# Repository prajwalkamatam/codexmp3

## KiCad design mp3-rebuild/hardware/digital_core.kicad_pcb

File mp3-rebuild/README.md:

# MP3 hardware rebuild — checkpoint, not a production release

This archive is NOT the completed MP3 player and is NOT a fabrication package.
It replaces the previous ad-hoc symbol recovery with a separately scoped digital
core schematic and a routed digital-core PCB prototype. The original complete-board
PCB is still invalid and must not be manufactured. No production-ready PCB,
Gerbers, or assembly files are supplied.

## Completed and checked

- Built a 52-symbol digital-core schematic (50 physical components plus two
  external-supply flags) with explicit pin assignments.
- Used Espressif's official ESP32-WROVER-E symbol and footprint, release 2.0.6,
  commit 3343256bd40fa1d049b444767d4b935ad93ba91f.
- Added EN reset RC, boot/reset switches, boot strapping, bias resistors,
  decoupling, battery ADC divider/filter, TCA9534 expander and seven buttons.
- Provided explicit interfaces for the intended GC9A01 display, SPI SD socket,
  regulated power, UART, I2S audio, and status signals. These interfaces are
  engineering boundaries, not substitutes for the missing product circuits.
- Bundled the symbol and footprint definitions required to open the schematic.
- KiCad 9.0.2 ERC: zero errors, zero warnings, exit status 0.
- KiCad XML export: completed with no annotation warning after reference cleanup.
- Exported connectivity: all 160 physical component-pin assignments match the
  digital-core connection model; specific ESP32 GPIO/reserved-pad assertions pass.
- Exported PDF and visually inspected the sheet. Zoom in for pin labels.
- Routed hardware/digital_core.kicad_pcb with 50 footprints and 36 named nets.
  KiCad 9.0.2 DRC with all severities and schematic parity reports zero
  violations, zero unconnected items and zero schematic parity issues.
  The underlying DRC command completed with exit status 0.
- Independently checked all 160 component-pin net assignments after importing
  copper. Reserved pads remain unassigned. See reports/routed-pad-check.txt.
- Routing was restored on 2026-11-14 using Freerouting 2.0.1. Both routing inputs
  and sessions are retained in engineering/. The ESP32 antenna keep-out is
  retained on both actual copper layers (F.Cu and B.Cu); the local library rule
  area was made specific to those two layers to match the board layer stack.
- The board remains a prototype with roomy 160 x 100 mm placement and 0.2 mm
  routing rules. Power-current capability, return paths, decoupling placement,
  and signal integrity require engineering review and physical validation.

Open hardware/digital_core.kicad_pro in KiCad 9 or newer. The project includes
hardware/digital_core.kicad_sch and hardware/digital_core.kicad_pcb.
See reports/digital-erc.txt, reports/digital-pcb-drc.txt, and
reports/netlist-check.txt for scoped evidence.
Open the extracted project with its matching .kicad_pcb, .kicad_sch and libraries
together. A .kicad_pro file contains project settings, not the routed copper.
Use the latest routed ZIP; the older GitHub commit 77369ca contains an unrouted PCB.
A clean ERC checks schematic rules; it does not prove analog performance,
component ratings, routing, power integrity, or physical operation.

## Historical datasheet-access blocker (not retested during routing)

During the earlier circuit-rebuild session, an HTTPS request to
https://www.ti.com/lit/ds/symlink/tpa6132a2.pdf returned
403 Forbidden at the proxy CONNECT stage. TLS checking was not disabled and the
network restriction was not bypassed.

Required manufacturer-domain additions were saved to the environment draft,
preserving the existing dl.espressif.com entry:
- www.ti.com
- ww1.microchip.com
- www.silabs.com
- www.waveshare.com
- files.waveshare.com
- www.espressif.com
- docs.espressif.com

Review/save the network changes in environment settings and publish the updated
environment configuration. A saved draft alone does not change running access.
After application, retest the affected request before resuming circuit selection.

## Remaining product work

1. Verify the exact Waveshare 1.28-inch GC9A01 module revision, supply, BL input,
   connector order, and mechanical drawing. J2 is the proposed carrier interface;
   do not connect an old ST7789 cable by position.
2. Select and verify the protected 1S 2000 mAh cell. Confirm 4.2 V termination,
   500 mA charging compatibility, temperature sensing, polarity and protection.
3. Rebuild the charger and load-sharing supply from manufacturer references.
   Evaluate MCP73871 power-path charging and a buck-boost regulator capable of
   the complete 3.3 V load at minimum battery voltage. The original AP2112 LDO
   does not maintain 3.3 V over the full single-cell discharge range. Do not
   finalize component values from symbol names or an ERC result.
4. Complete PCM5102A analog supplies, charge pump, output filtering and mode pins.
   Evaluate TPA6132A2 as a concrete headphone-amplifier replacement for the
   original invalid MAX97220A MPN/footprint combination, using its datasheet.
5. Complete the USB-C CC termination, ESD, CP2102N supplies and programming
   circuit, and the actual microSD and headphone socket circuits.
6. Merge sheets into the full product schematic, resolve the complete BOM,
   verify every symbol-to-pad mapping and run full-design ERC.
7. Place and route a new PCB from that verified netlist. Preserve RF antenna
   exclusion, switching-current loops, continuous return paths, analog layout,
   connector mechanics and required thermal copper. Run full DRC and parity.
8. Generate fabrication/assembly outputs only from the final checked board.
9. Implement missing firmware functionality: audio_player_play_file currently
   only updates metadata/state and uses a hardcoded duration. There is no MP3
   decoder producer feeding the PCM ring buffer. The Bluetooth path only delays.
   The display driver remains ST7789-specific. These are confirmed source-code
   gaps, not environment failures.
10. Build and test a prototype: current-limited rail bring-up, charger termination
    and temperature behavior, boot/flash, GC9A01 display, SD access, decoded wired
    and Bluetooth audio, RF operation, noise, battery life and thermal margins.

## Reproduction

With Python 3 and KiCad 9.0.2 standard libraries installed:
  python3 build_digital.py
  kicad-cli sch erc --exit-code-violations -o reports/digital-erc.txt hardware/digital_core.kicad_sch
  kicad-cli sch export netlist --format kicadxml -o engineering/digital_core.xml hardware/digital_core.kicad_sch
  python3 check_netlist.py
  /usr/bin/python3 build_pcb.py
  /usr/bin/python3 apply_routing.py engineering/digital_core.ses
  /usr/bin/python3 apply_routing.py engineering/finish.ses
  kicad-cli pcb drc --schematic-parity --severity-all --exit-code-violations -o reports/digital-pcb-drc.txt hardware/digital_core.kicad_pcb
  kicad-cli sch export pdf -o engineering/digital_core.pdf hardware/digital_core.kicad_sch

Run KiCad commands sequentially because they can update project settings.
The routing sessions apply only to the current component positions and netlist.
If you change either, generate new routing rather than replaying the sessions.
Preserve the bundled official footprint under hardware/libraries/Local.pretty.
3D model paths in standard footprints may refer to an installed KiCad model pack;
3D model availability was not validated and is not included in the ERC claim.

Source licenses and Espressif release source are in sources/. The original
repository's tracked mp3.zip was preserved. This checkpoint makes no certification,
production-release, or end-to-end functionality claim.

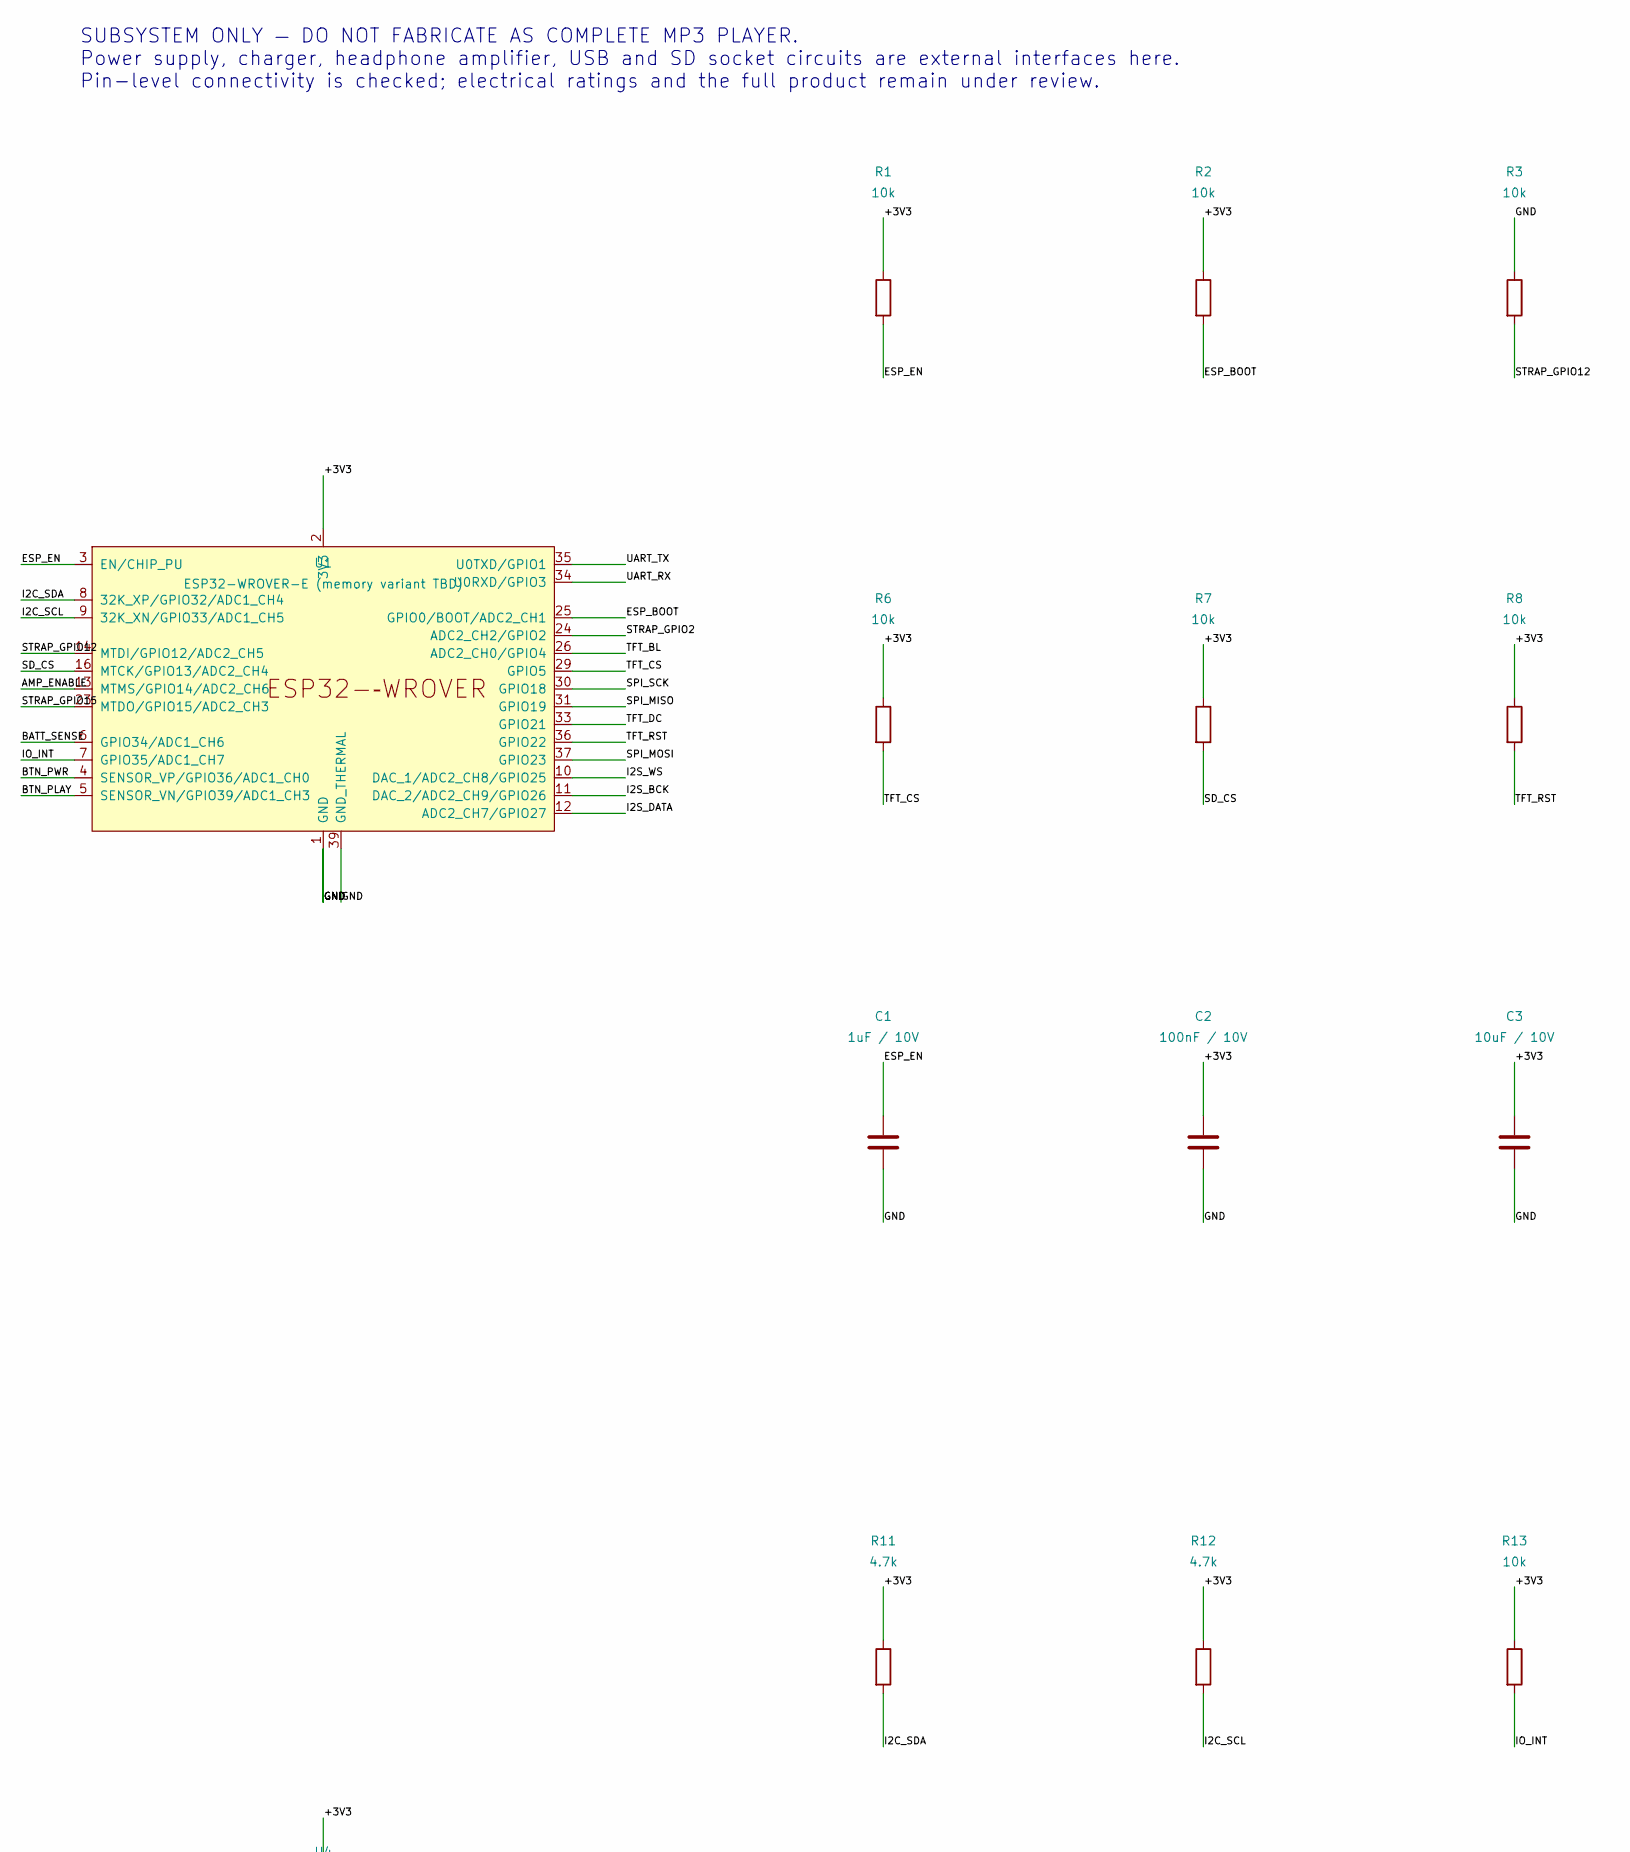
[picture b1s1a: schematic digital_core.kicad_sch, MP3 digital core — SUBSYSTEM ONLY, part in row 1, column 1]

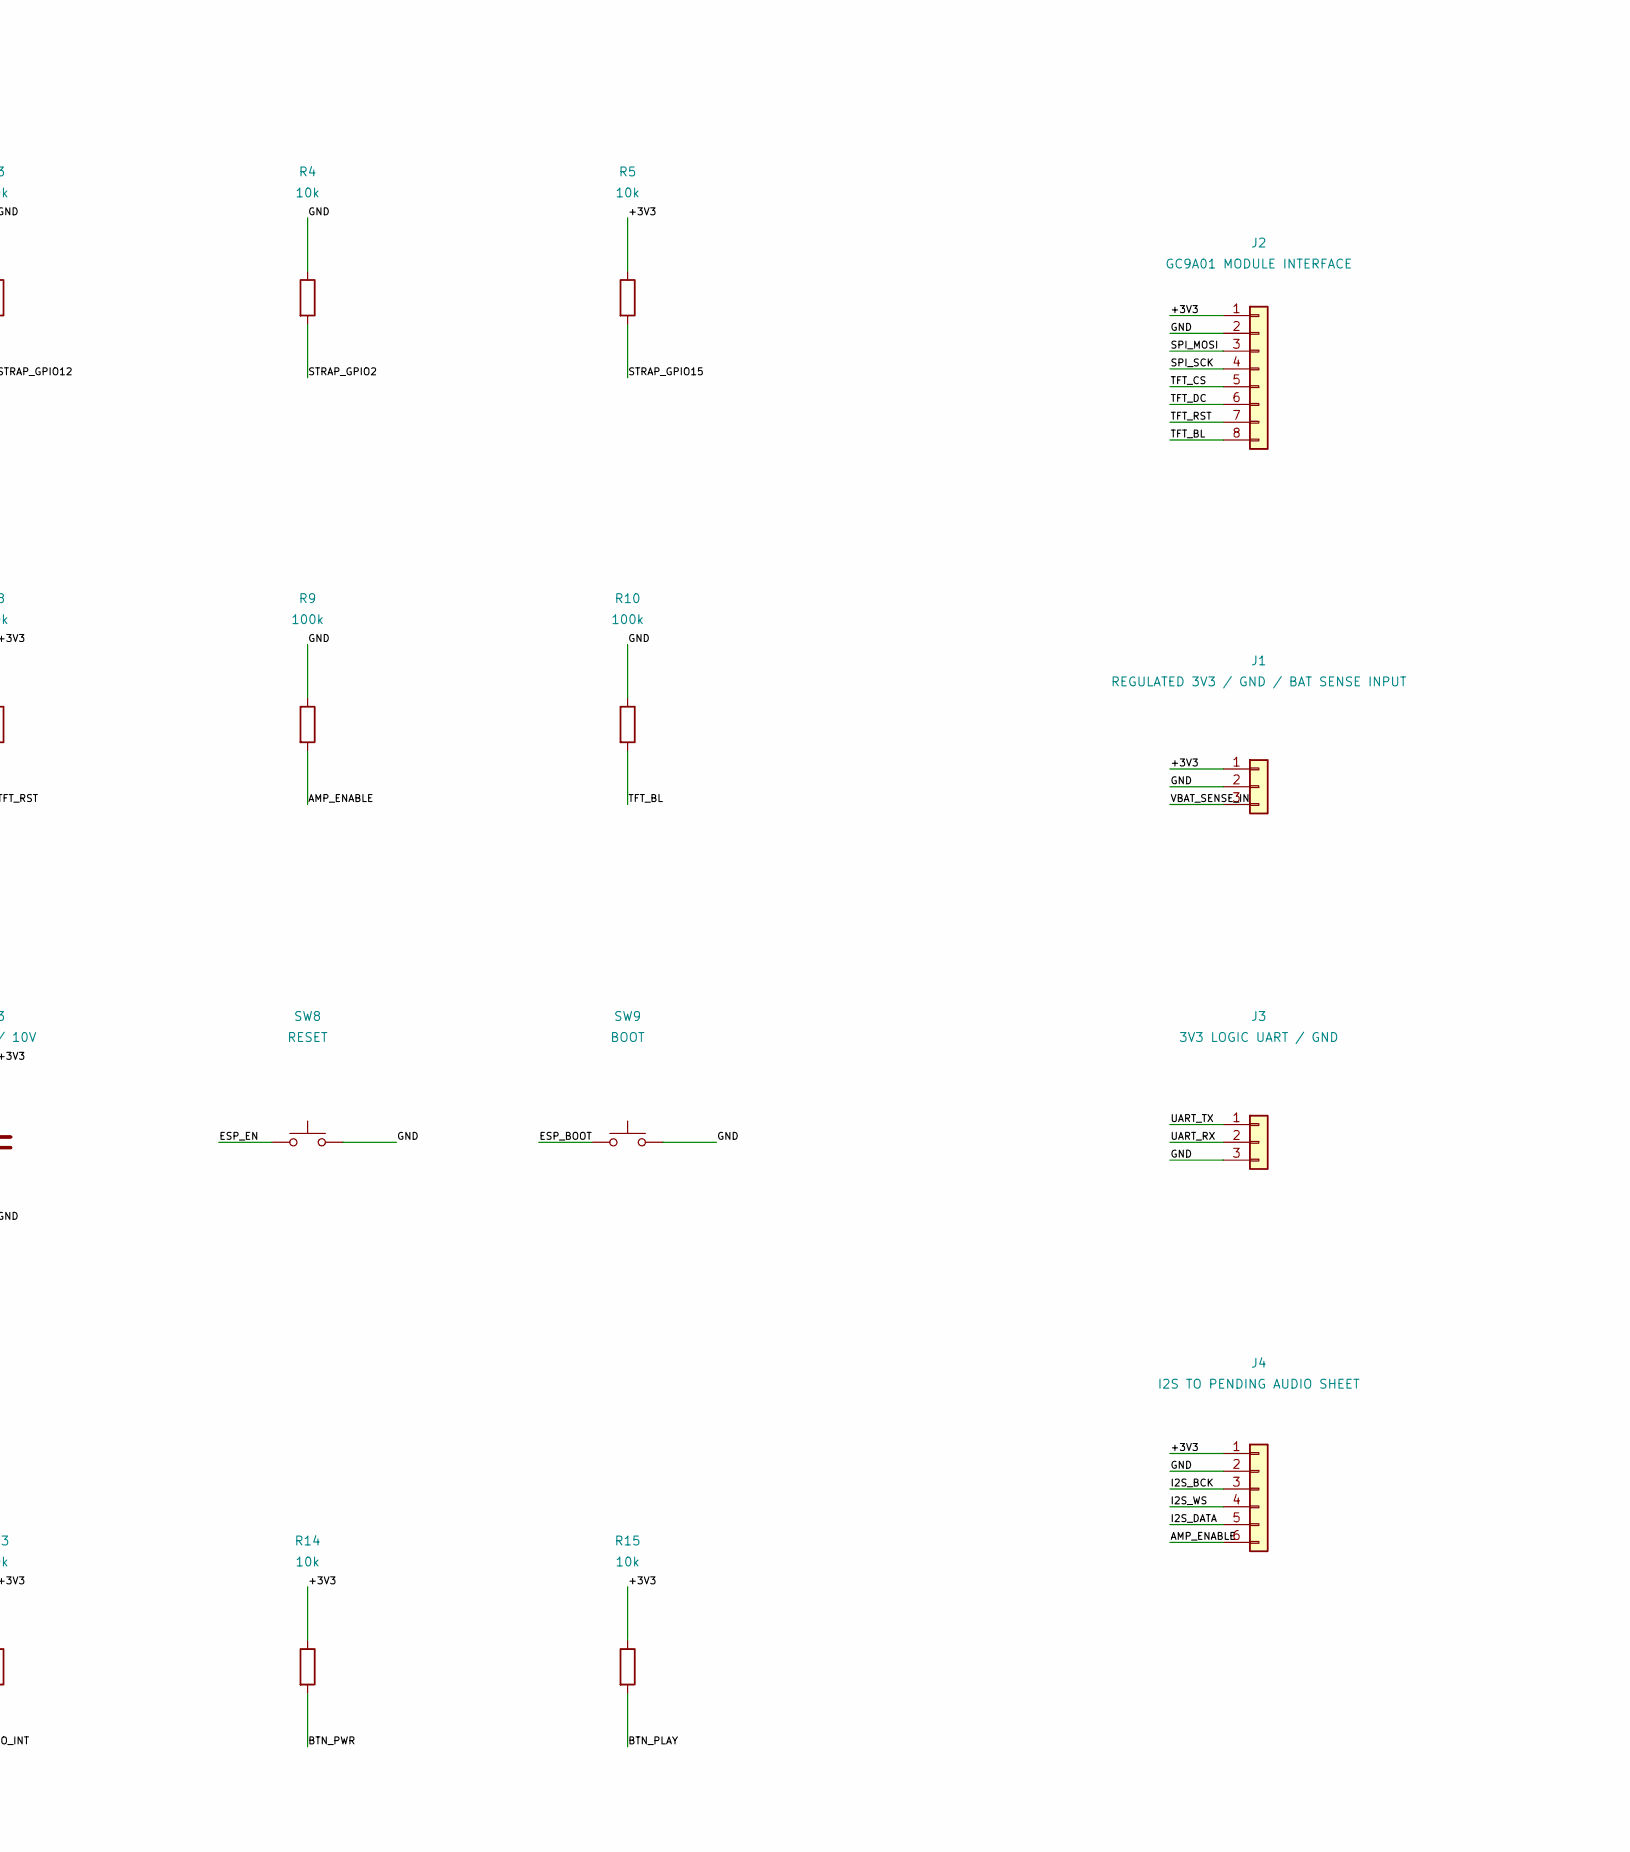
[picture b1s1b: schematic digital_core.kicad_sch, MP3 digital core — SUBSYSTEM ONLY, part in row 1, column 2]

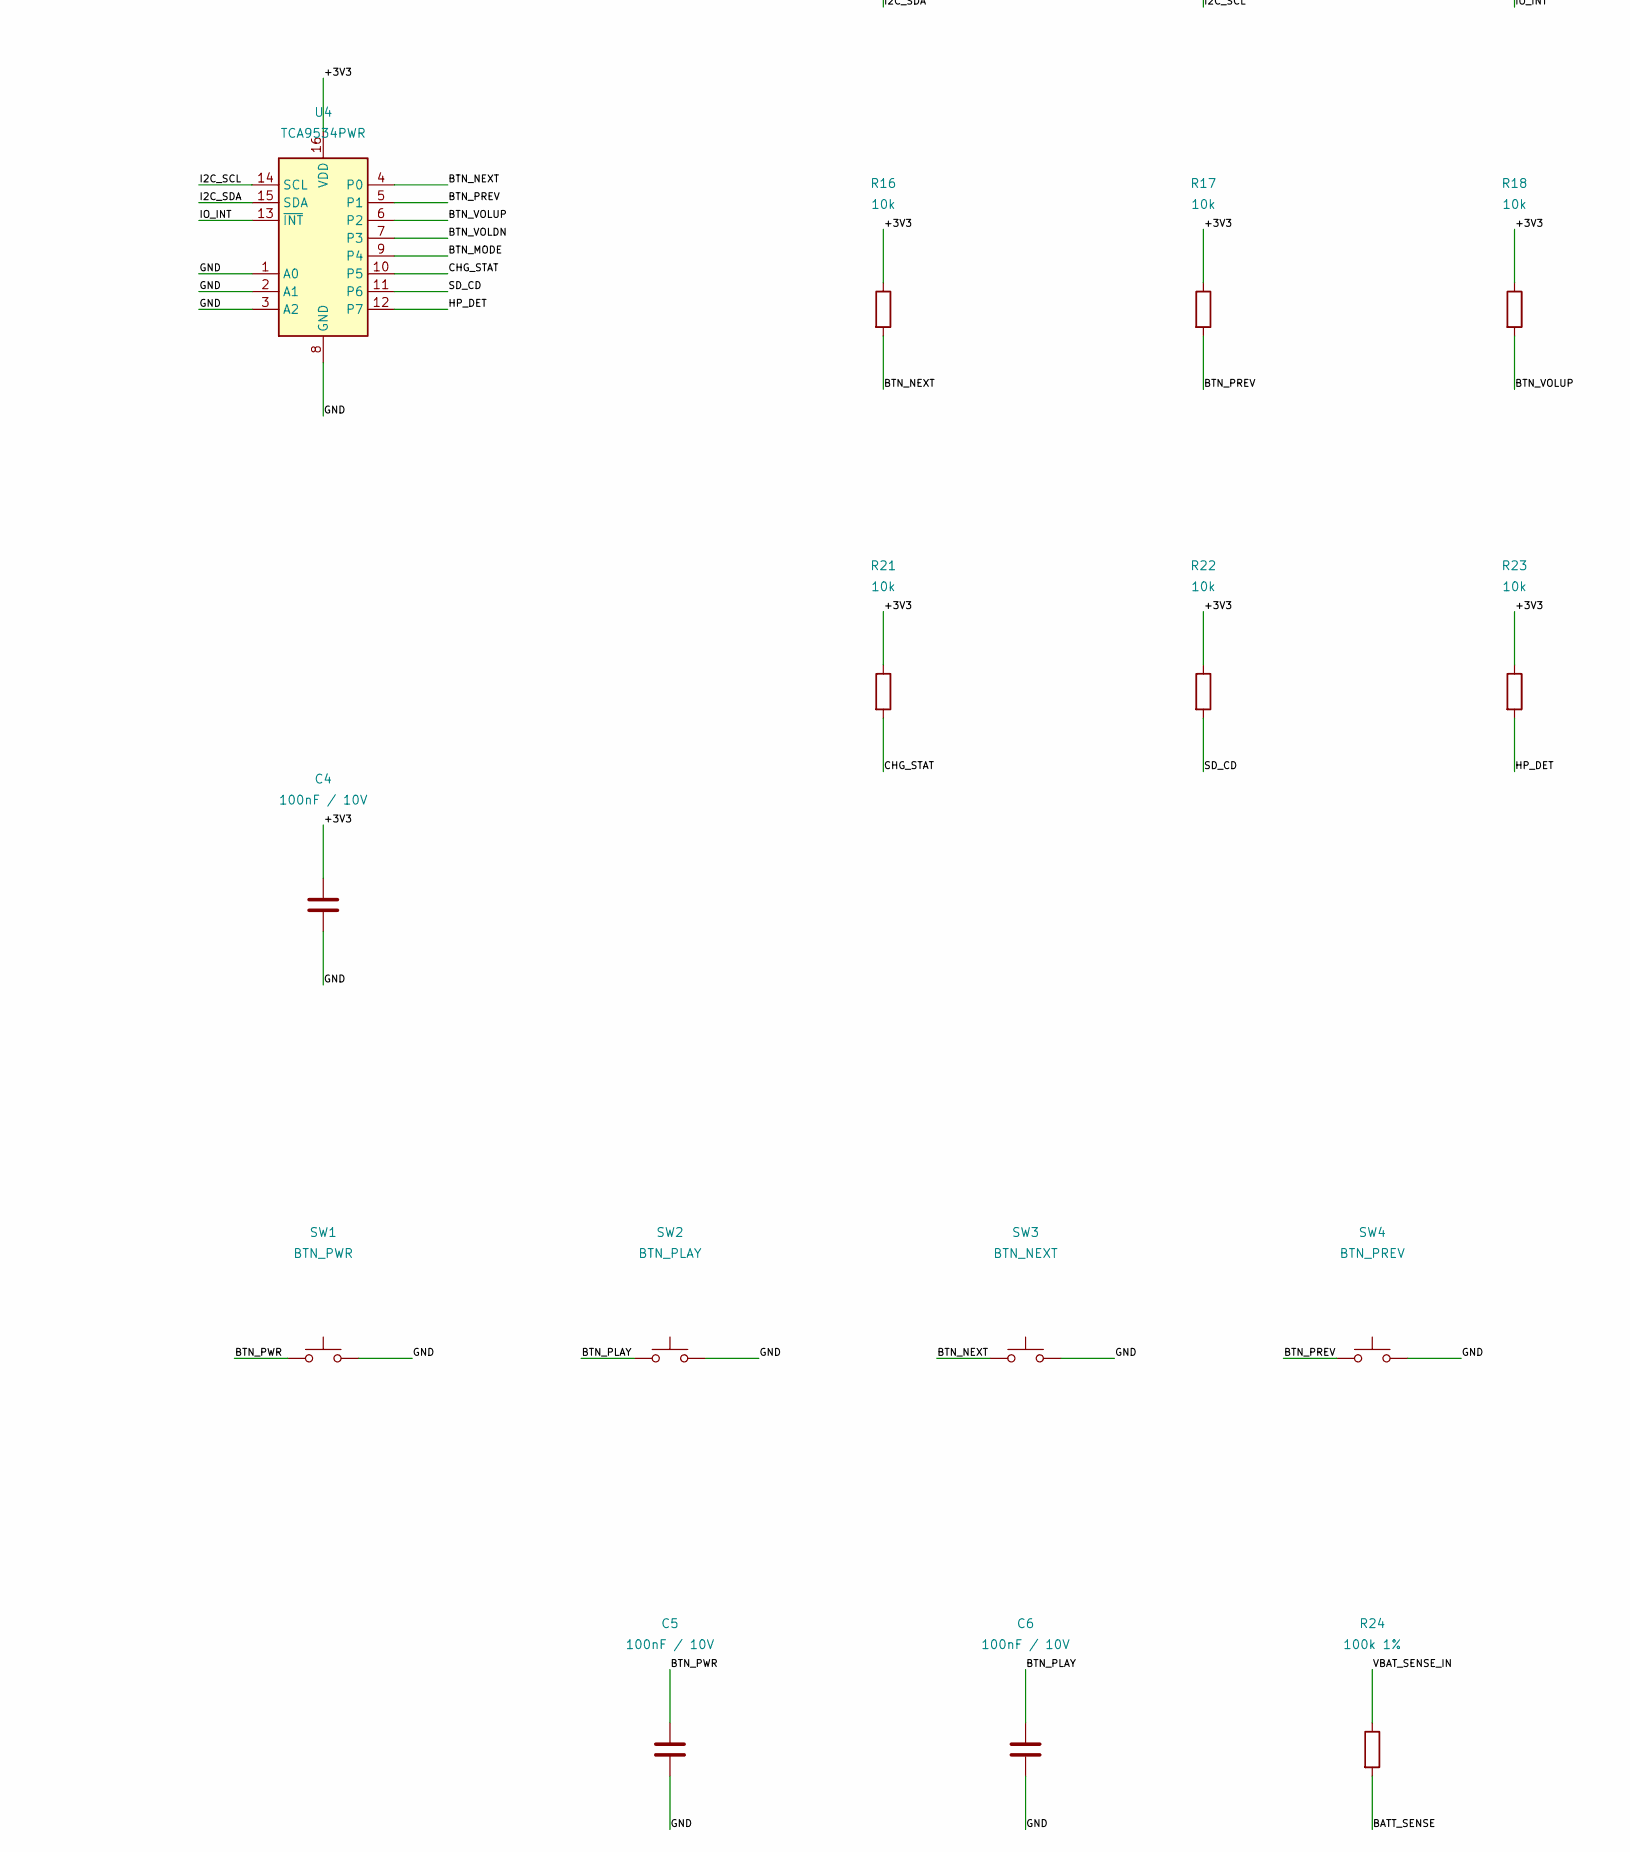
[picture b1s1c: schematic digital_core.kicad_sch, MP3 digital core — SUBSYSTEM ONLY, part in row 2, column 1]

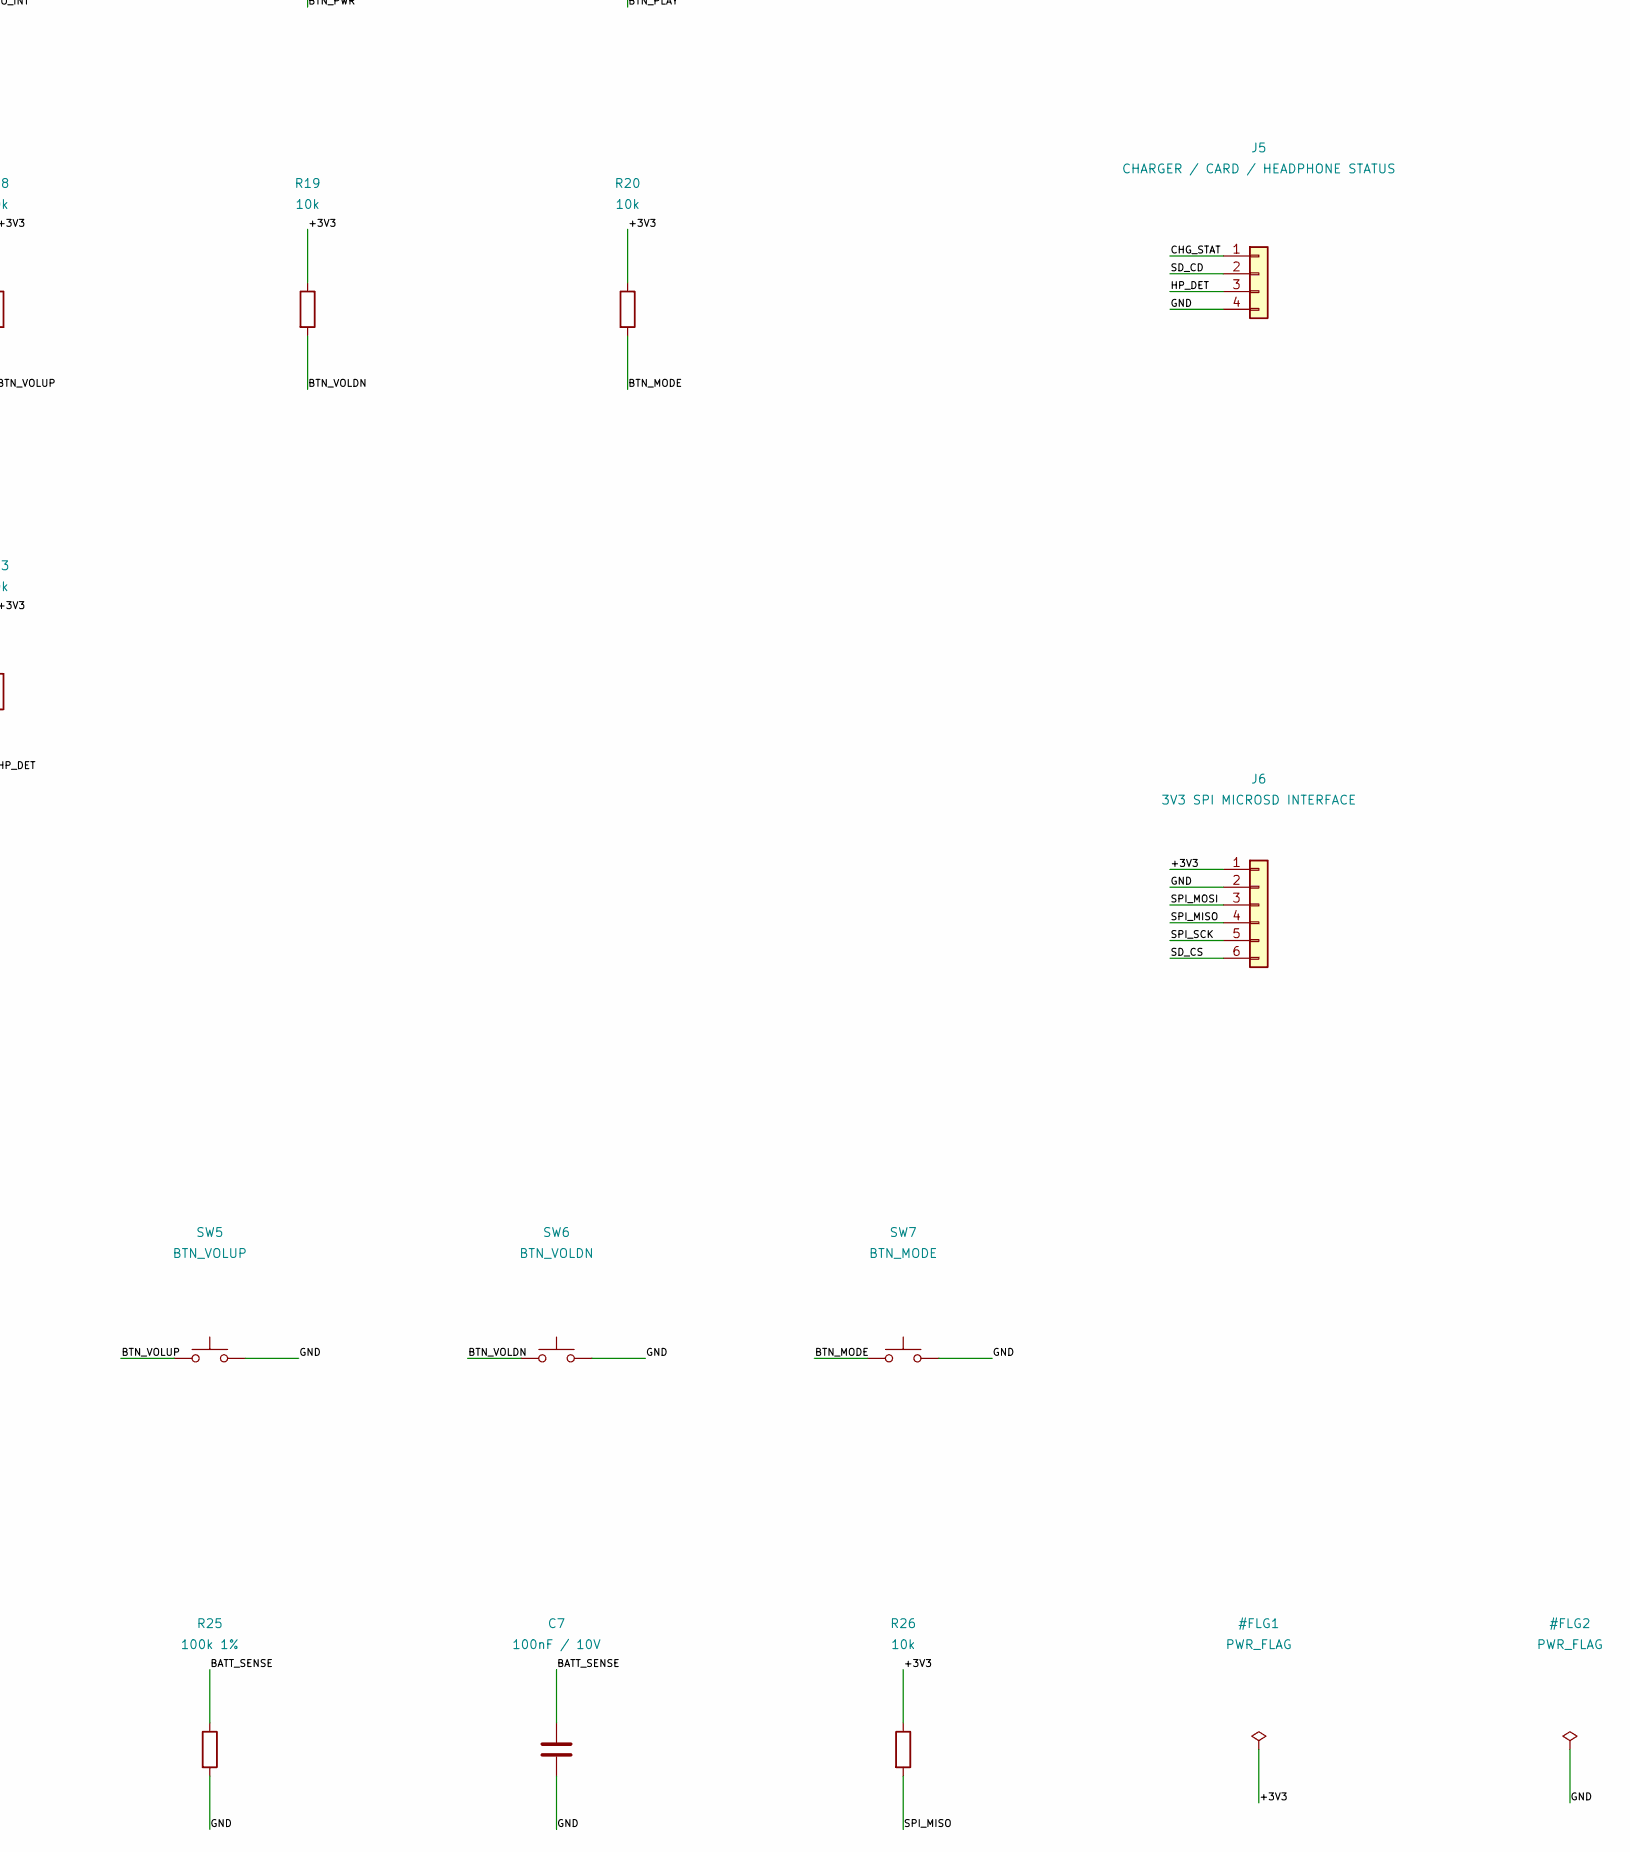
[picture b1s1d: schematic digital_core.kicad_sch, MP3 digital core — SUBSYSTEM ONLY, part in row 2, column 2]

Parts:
C1: 1uF / 10V; C_0603_1608Metric
C2, C4, C5, C6, C7: 100nF / 10V; C_0603_1608Metric
C3: 10uF / 10V; C_0805_2012Metric
J1: REGULATED 3V3 / GND / BAT SENSE INPUT; PinHeader_1x03_P2.54mm_Vertical
J2: GC9A01 MODULE INTERFACE; PinHeader_1x08_P2.54mm_Vertical
J3: 3V3 LOGIC UART / GND; PinHeader_1x03_P2.54mm_Vertical
J4: I2S TO PENDING AUDIO SHEET; PinHeader_1x06_P2.54mm_Vertical
J5: CHARGER / CARD / HEADPHONE STATUS; PinHeader_1x04_P2.54mm_Vertical
J6: 3V3 SPI MICROSD INTERFACE; PinHeader_1x06_P2.54mm_Vertical
R1, R2, R3, R4, R5, R6, R7, R8, R13, R14, R15, R16, R17, R18, R19, R20, R21, R22, R23, R26: 10k; R_0603_1608Metric
R9, R10: 100k; R_0603_1608Metric
R11, R12: 4.7k; R_0603_1608Metric
R24, R25: 100k 1%; R_0603_1608Metric
SW1: BTN_PWR; SW_SPST_TL3342
SW2: BTN_PLAY; SW_SPST_TL3342
SW3: BTN_NEXT; SW_SPST_TL3342
SW4: BTN_PREV; SW_SPST_TL3342
SW5: BTN_VOLUP; SW_SPST_TL3342
SW6: BTN_VOLDN; SW_SPST_TL3342
SW7: BTN_MODE; SW_SPST_TL3342
SW8: RESET; SW_SPST_TL3342
SW9: BOOT; SW_SPST_TL3342
U1: ESP32-WROVER-E (memory variant TBD); ESP32-WROVER-E
U4: TCA9534PWR; TSSOP-16_4.4x5mm_P0.65mm

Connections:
/+3V3: C2.1, C3.1, C4.1, J1.1, J2.1, J4.1, J6.1, R1.1, R2.1, R5.1, R6.1, R7.1, R8.1, R11.1, R12.1, R13.1, R14.1, R15.1, R16.1, R17.1, R18.1, R19.1, R20.1, R21.1, R22.1, R23.1, R26.1, U1.2 (3V3), U4.16 (VDD)
/AMP_ENABLE: J4.6, R9.2, U1.13 (MTMS/GPIO14/ADC2_CH6)
/BATT_SENSE: C7.1, R24.2, R25.1, U1.6 (GPIO34/ADC1_CH6)
/BTN_MODE: R20.2, SW7.1, U4.9 (P4)
/BTN_NEXT: R16.2, SW3.1, U4.4 (P0)
/BTN_PLAY: C6.1, R15.2, SW2.1, U1.5 (SENSOR_VN/GPIO39/ADC1_CH3)
/BTN_PREV: R17.2, SW4.1, U4.5 (P1)
/BTN_PWR: C5.1, R14.2, SW1.1, U1.4 (SENSOR_VP/GPIO36/ADC1_CH0)
/BTN_VOLDN: R19.2, SW6.1, U4.7 (P3)
/BTN_VOLUP: R18.2, SW5.1, U4.6 (P2)
/CHG_STAT: J5.1, R21.2, U4.10 (P5)
/ESP_BOOT: R2.2, SW9.1, U1.25 (GPIO0/BOOT/ADC2_CH1)
/ESP_EN: C1.1, R1.2, SW8.1, U1.3 (EN/CHIP_PU)
/GND: C1.2, C2.2, C3.2, C4.2, C5.2, C6.2, C7.2, J1.2, J2.2, J3.3, J4.2, J5.4, J6.2, R3.1, R4.1, R9.1, R10.1, R25.2, SW1.2, SW2.2, SW3.2, SW4.2, SW5.2, SW6.2, SW7.2, SW8.2, SW9.2, U1.1 (GND), U1.15 (GND), U1.38 (GND), U1.39 (GND_THERMAL), U4.1 (A0), U4.2 (A1), U4.3 (A2), U4.8 (GND)
/HP_DET: J5.3, R23.2, U4.12 (P7)
/I2C_SCL: R12.2, U1.9 (32K_XN/GPIO33/ADC1_CH5), U4.14 (SCL)
/I2C_SDA: R11.2, U1.8 (32K_XP/GPIO32/ADC1_CH4), U4.15 (SDA)
/I2S_BCK: J4.3, U1.11 (DAC_2/ADC2_CH9/GPIO26)
/I2S_DATA: J4.5, U1.12 (ADC2_CH7/GPIO27)
/I2S_WS: J4.4, U1.10 (DAC_1/ADC2_CH8/GPIO25)
/IO_INT: R13.2, U1.7 (GPIO35/ADC1_CH7), U4.13 (~INT)
/SD_CD: J5.2, R22.2, U4.11 (P6)
/SD_CS: J6.6, R7.2, U1.16 (MTCK/GPIO13/ADC2_CH4)
/SPI_MISO: J6.4, R26.2, U1.31 (GPIO19)
/SPI_MOSI: J2.3, J6.3, U1.37 (GPIO23)
/SPI_SCK: J2.4, J6.5, U1.30 (GPIO18)
/STRAP_GPIO2: R4.2, U1.24 (ADC2_CH2/GPIO2)
/STRAP_GPIO12: R3.2, U1.14 (MTDI/GPIO12/ADC2_CH5)
/STRAP_GPIO15: R5.2, U1.23 (MTDO/GPIO15/ADC2_CH3)
/TFT_BL: J2.8, R10.2, U1.26 (ADC2_CH0/GPIO4)
/TFT_CS: J2.5, R6.2, U1.29 (GPIO5)
/TFT_DC: J2.6, U1.33 (GPIO21)
/TFT_RST: J2.7, R8.2, U1.36 (GPIO22)
/UART_RX: J3.2, U1.34 (U0RXD/GPIO3)
/UART_TX: J3.1, U1.35 (U0TXD/GPIO1)
/VBAT_SENSE_IN: J1.3, R24.1

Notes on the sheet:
SUBSYSTEM ONLY — DO NOT FABRICATE AS COMPLETE MP3 PLAYER. Power supply, charger, headphone amplifier, USB and SD socket circuits are external interfaces here. Pin-level connectivity is checked; electrical ratings and the full product remain under review.

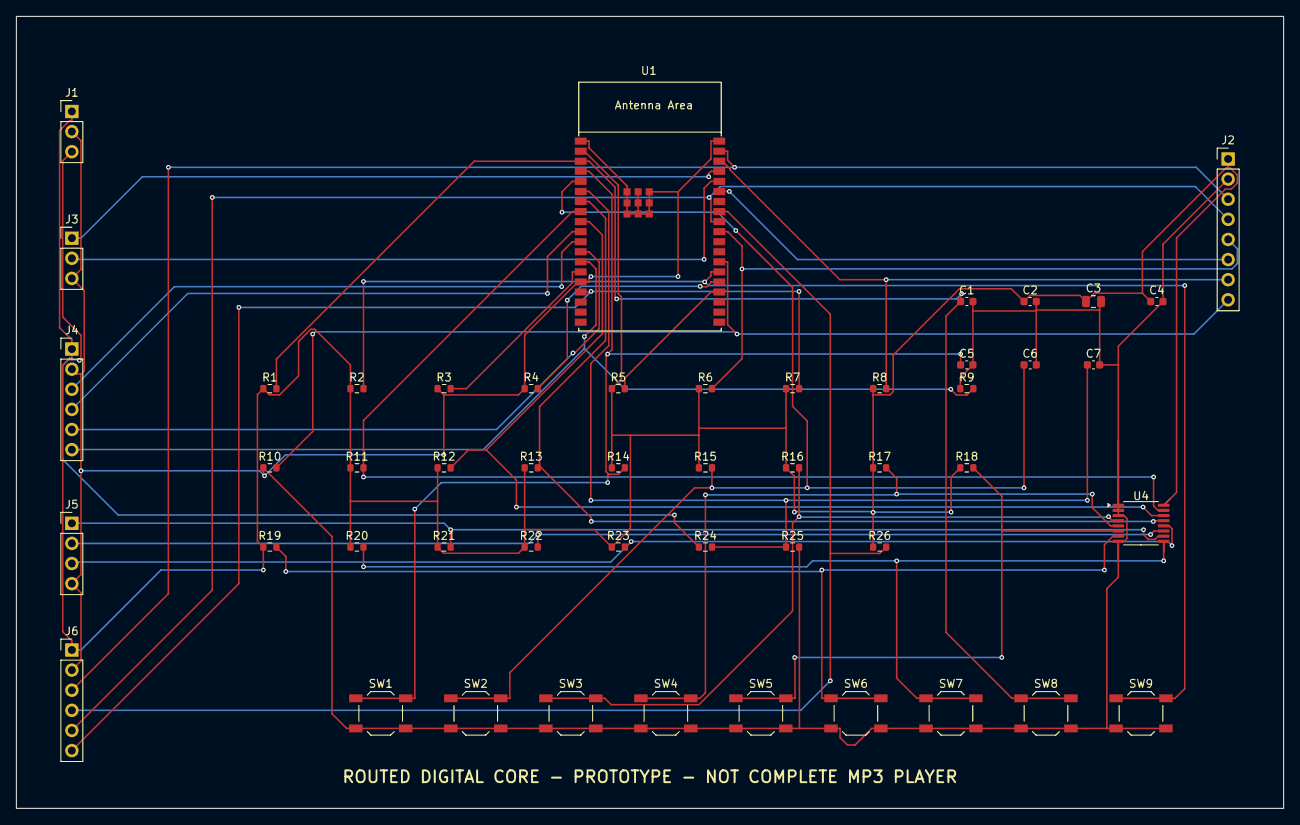
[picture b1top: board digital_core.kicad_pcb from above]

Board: 2 copper layers, 160.0 x 100.0 mm, 50 parts (0 on the bottom side), 36 nets.

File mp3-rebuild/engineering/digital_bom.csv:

Reference,Value,Footprint,Scope
U1,ESP32-WROVER-E (memory variant TBD),Local:ESP32-WROVER-E,DIGITAL SUBSYSTEM DRAFT
R1,10k,Local:R_0603_1608Metric,DIGITAL SUBSYSTEM DRAFT
R2,10k,Local:R_0603_1608Metric,DIGITAL SUBSYSTEM DRAFT
R3,10k,Local:R_0603_1608Metric,DIGITAL SUBSYSTEM DRAFT
R4,10k,Local:R_0603_1608Metric,DIGITAL SUBSYSTEM DRAFT
R5,10k,Local:R_0603_1608Metric,DIGITAL SUBSYSTEM DRAFT
R6,10k,Local:R_0603_1608Metric,DIGITAL SUBSYSTEM DRAFT
R7,10k,Local:R_0603_1608Metric,DIGITAL SUBSYSTEM DRAFT
R8,10k,Local:R_0603_1608Metric,DIGITAL SUBSYSTEM DRAFT
R9,100k,Local:R_0603_1608Metric,DIGITAL SUBSYSTEM DRAFT
R10,100k,Local:R_0603_1608Metric,DIGITAL SUBSYSTEM DRAFT
C1,1uF / 10V,Local:C_0603_1608Metric,DIGITAL SUBSYSTEM DRAFT
C2,100nF / 10V,Local:C_0603_1608Metric,DIGITAL SUBSYSTEM DRAFT
C3,10uF / 10V,Local:C_0805_2012Metric,DIGITAL SUBSYSTEM DRAFT
SW8,RESET,Local:SW_SPST_TL3342,DIGITAL SUBSYSTEM DRAFT
SW9,BOOT,Local:SW_SPST_TL3342,DIGITAL SUBSYSTEM DRAFT
J2,GC9A01 MODULE INTERFACE,Local:PinHeader_1x08_P2.54mm_Vertical,DIGITAL SUBSYSTEM DRAFT
J1,REGULATED 3V3 / GND / BAT SENSE INPUT,Local:PinHeader_1x03_P2.54mm_Vertical,DIGITAL SUBSYSTEM DRAFT
J3,3V3 LOGIC UART / GND,Local:PinHeader_1x03_P2.54mm_Vertical,DIGITAL SUBSYSTEM DRAFT
J4,I2S TO PENDING AUDIO SHEET,Local:PinHeader_1x06_P2.54mm_Vertical,DIGITAL SUBSYSTEM DRAFT
U4,TCA9534PWR,Local:TSSOP-16_4.4x5mm_P0.65mm,DIGITAL SUBSYSTEM DRAFT
R11,4.7k,Local:R_0603_1608Metric,DIGITAL SUBSYSTEM DRAFT
R12,4.7k,Local:R_0603_1608Metric,DIGITAL SUBSYSTEM DRAFT
R13,10k,Local:R_0603_1608Metric,DIGITAL SUBSYSTEM DRAFT
R14,10k,Local:R_0603_1608Metric,DIGITAL SUBSYSTEM DRAFT
R15,10k,Local:R_0603_1608Metric,DIGITAL SUBSYSTEM DRAFT
R16,10k,Local:R_0603_1608Metric,DIGITAL SUBSYSTEM DRAFT
R17,10k,Local:R_0603_1608Metric,DIGITAL SUBSYSTEM DRAFT
R18,10k,Local:R_0603_1608Metric,DIGITAL SUBSYSTEM DRAFT
R19,10k,Local:R_0603_1608Metric,DIGITAL SUBSYSTEM DRAFT
R20,10k,Local:R_0603_1608Metric,DIGITAL SUBSYSTEM DRAFT
R21,10k,Local:R_0603_1608Metric,DIGITAL SUBSYSTEM DRAFT
R22,10k,Local:R_0603_1608Metric,DIGITAL SUBSYSTEM DRAFT
R23,10k,Local:R_0603_1608Metric,DIGITAL SUBSYSTEM DRAFT
SW1,BTN_PWR,Local:SW_SPST_TL3342,DIGITAL SUBSYSTEM DRAFT
SW2,BTN_PLAY,Local:SW_SPST_TL3342,DIGITAL SUBSYSTEM DRAFT
SW3,BTN_NEXT,Local:SW_SPST_TL3342,DIGITAL SUBSYSTEM DRAFT
SW4,BTN_PREV,Local:SW_SPST_TL3342,DIGITAL SUBSYSTEM DRAFT
SW5,BTN_VOLUP,Local:SW_SPST_TL3342,DIGITAL SUBSYSTEM DRAFT
SW6,BTN_VOLDN,Local:SW_SPST_TL3342,DIGITAL SUBSYSTEM DRAFT
SW7,BTN_MODE,Local:SW_SPST_TL3342,DIGITAL SUBSYSTEM DRAFT
C4,100nF / 10V,Local:C_0603_1608Metric,DIGITAL SUBSYSTEM DRAFT
C5,100nF / 10V,Local:C_0603_1608Metric,DIGITAL SUBSYSTEM DRAFT
C6,100nF / 10V,Local:C_0603_1608Metric,DIGITAL SUBSYSTEM DRAFT
R24,100k 1%,Local:R_0603_1608Metric,DIGITAL SUBSYSTEM DRAFT
R25,100k 1%,Local:R_0603_1608Metric,DIGITAL SUBSYSTEM DRAFT
C7,100nF / 10V,Local:C_0603_1608Metric,DIGITAL SUBSYSTEM DRAFT
J5,CHARGER / CARD / HEADPHONE STATUS,Local:PinHeader_1x04_P2.54mm_Vertical,DIGITAL SUBSYSTEM DRAFT
J6,3V3 SPI MICROSD INTERFACE,Local:PinHeader_1x06_P2.54mm_Vertical,DIGITAL SUBSYSTEM DRAFT
R26,10k,Local:R_0603_1608Metric,DIGITAL SUBSYSTEM DRAFT

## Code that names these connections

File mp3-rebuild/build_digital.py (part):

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def c(ref,val,a,b,x,y): add(ref,'Device','C',val,CFP,{1:a,2:b},x,y,'decoupling')
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add('U1','Espressif','ESP32-WROVER-E','ESP32-WROVER-E (memory variant TBD)','Local:ESP32-WROVER-E',mcunets,70,110,'MCU')
for i,(net,rail,val) in enumerate([('ESP_EN','+3V3','10k'),('ESP_BOOT','+3V3','10k'),('STRAP_GPIO12','GND','10k'),('STRAP_GPIO2','GND','10k'),('STRAP_GPIO15','+3V3','10k'),('TFT_CS','+3V3','10k'),('SD_CS','+3V3','10k'),('TFT_RST','+3V3','10k'),('AMP_ENABLE','GND','100k'),('TFT_BL','GND','100k')]):
 r('R'+str(i+1),val,rail,net,150+(i%5)*45,55+(i//5)*60)
c('C1','1uF / 10V','ESP_EN','GND',150,175)
c('C2','100nF / 10V','+3V3','GND',195,175)
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add('SW8','Switch','SW_Push','RESET',SWFP,{1:'ESP_EN',2:'GND'},285,175,'reset')
add('SW9','Switch','SW_Push','BOOT',SWFP,{1:'ESP_BOOT',2:'GND'},330,175,'reset')
# Display carrier connector: logical interface only; purchased module pin order remains a datasheet gate.
add('J2','Connector_Generic','Conn_01x08','GC9A01 MODULE INTERFACE','Connector_PinHeader_2.54mm:PinHeader_1x08_P2.54mm_Vertical',{1:'+3V3',2:'GND',3:'SPI_MOSI',4:'SPI_SCK',5:'TFT_CS',6:'TFT_DC',7:'TFT_RST',8:'TFT_BL'},420,65,'display')
# Explicit external interfaces keep the unverified power/audio/USB circuits outside this subsystem.
add('J1','Connector_Generic','Conn_01x03','REGULATED 3V3 / GND / BAT SENSE INPUT','Connector_PinHeader_2.54mm:PinHeader_1x03_P2.54mm_Vertical',{1:'+3V3',2:'GND',3:'VBAT_SENSE_IN'},420,125,'external power')
add('J3','Connector_Generic','Conn_01x03','3V3 LOGIC UART / GND','Connector_PinHeader_2.54mm:PinHeader_1x03_P2.54mm_Vertical',{1:'UART_TX',2:'UART_RX',3:'GND'},420,175,'external USB-UART')
add('J4','Connector_Generic','Conn_01x06','I2S TO PENDING AUDIO SHEET','Connector_PinHeader_2.54mm:PinHeader_1x06_P2.54mm_Vertical',{1:'+3V3',2:'GND',3:'I2S_BCK',4:'I2S_WS',5:'I2S_DATA',6:'AMP_ENABLE'},420,225,'external audio')
add('U4','Interface_Expansion','TCA9534','TCA9534PWR','Package_SO:TSSOP-16_4.4x5mm_P0.65mm',{1:'GND',2:'GND',3:'GND',4:'BTN_NEXT',5:'BTN_PREV',6:'BTN_VOLUP',7:'BTN_VOLDN',8:'GND',9:'BTN_MODE',10:'CHG_STAT',11:'SD_CD',12:'HP_DET',13:'IO_INT',14:'I2C_SCL',15:'I2C_SDA',16:'+3V3'},70,295,'buttons')
for i,net in enumerate(['I2C_SDA','I2C_SCL','IO_INT','BTN_PWR','BTN_PLAY','BTN_NEXT','BTN_PREV','BTN_VOLUP','BTN_VOLDN','BTN_MODE','CHG_STAT','SD_CD','HP_DET']):
 r('R'+str(i+11),'4.7k' if i<2 else '10k','+3V3',net,150+(i%5)*45,250+(i//5)*55)
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r('R24','100k 1%','VBAT_SENSE_IN','BATT_SENSE',220,510)
r('R25','100k 1%','BATT_SENSE','GND',270,510)
c('C7','100nF / 10V','BATT_SENSE','GND',320,510)
add('J5','Connector_Generic','Conn_01x04','CHARGER / CARD / HEADPHONE STATUS','Connector_PinHeader_2.54mm:PinHeader_1x04_P2.54mm_Vertical',{1:'CHG_STAT',2:'SD_CD',3:'HP_DET',4:'GND'},420,300,'external status')
add('J6','Connector_Generic','Conn_01x06','3V3 SPI MICROSD INTERFACE','Connector_PinHeader_2.54mm:PinHeader_1x06_P2.54mm_Vertical',{1:'+3V3',2:'GND',3:'SPI_MOSI',4:'SPI_MISO',5:'SPI_SCK',6:'SD_CS'},420,390,'external SD socket')
r('R26','10k','+3V3','SPI_MISO',370,510)
# Flags represent the regulated external supply at J1, not a fictitious on-board regulator.
for i,net in enumerate(['+3V3','GND']): add('#FLG'+str(i+1),'power','PWR_FLAG','PWR_FLAG','',{1:net},420+i*45,510,'power source declaration')
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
